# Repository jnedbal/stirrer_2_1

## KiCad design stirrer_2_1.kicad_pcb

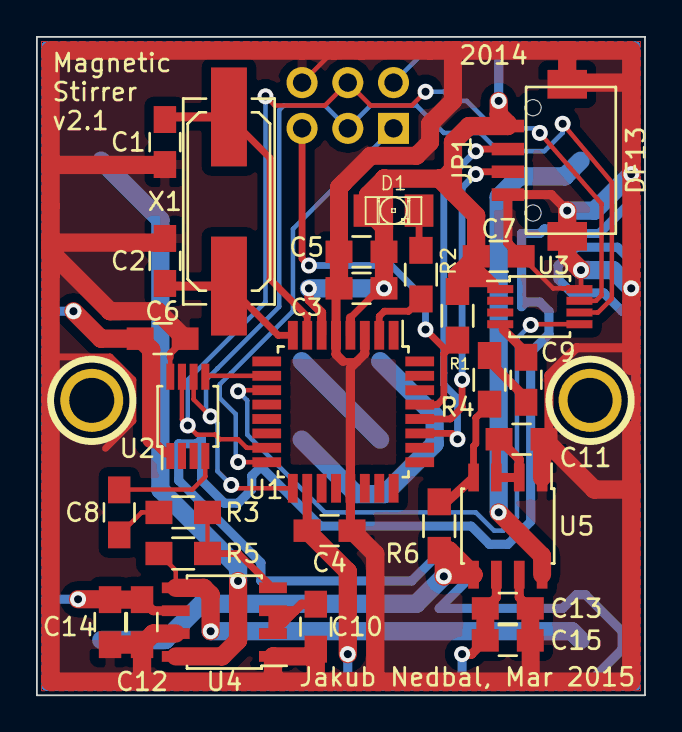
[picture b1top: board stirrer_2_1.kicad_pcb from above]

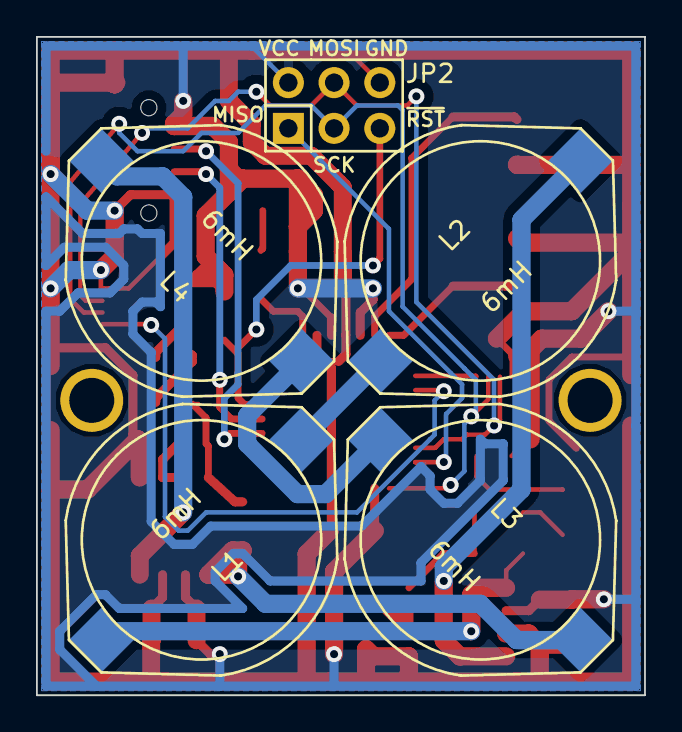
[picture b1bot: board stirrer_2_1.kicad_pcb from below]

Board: 2 copper layers, 33.8 x 36.6 mm, 36 parts (5 on the bottom side), 28 nets.

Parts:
C1, C2: 18p; C_0805_HandSoldering
C3, C4, C6, C7, C12, C13: 100n; C_0805_HandSoldering
C5, C8, C9, C14, C15: 10u; C_0805_HandSoldering
C10, C11: 470n; C_0805_HandSoldering
D1: LED 1206 yel; LED-1206
JP1: DF13; DF13-4P-1.25H
JP2: CONN_3X2; Pin_Header_Straight_2x03
L1, L2, L3, L4: 6mH; 6mH_coil
P1, P2: CONN_1; 1pin
R1: 10k; R_0805_HandSoldering
R2: 470R; R_0805_HandSoldering
R3, R4: 33k; R_0805_HandSoldering
R5, R6: 22k; R_0805_HandSoldering
U1: ATMEGA328P; TQFP-32_7x7mm_Pitch0.8mm
U2, U3: DAC101S101; MSOP-8_3x3mm_Pitch0.65mm
U4, U5: TPA301; SOIC-8_3.9x4.9mm_Pitch1.27mm
X1: 8.000MHz; Q_49U3HMS

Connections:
/MISO: JP2.1, U1.16
/RESET: JP2.5, R1.2, U1.29
/powerModule_2_1/AIN1: C8.2, R3.1
/powerModule_2_1/AIN2: C9.2, R4.1
/powerModule_2_1/DACOUT1: C8.1, U2.4
/powerModule_2_1/DACOUT2: C9.1, U3.4
/powerModule_2_1/IN1+: C10.1, U4.2, U4.3
/powerModule_2_1/IN1-: R3.2, R5.1, U4.4
/powerModule_2_1/IN2+: C11.1, U5.2, U5.3
/powerModule_2_1/IN2-: R4.2, R6.1, U5.4
/powerModule_2_1/L12_VO+: L1.1, R5.2, U4.5
/powerModule_2_1/L12_VO-: L2.1, U4.8
/powerModule_2_1/L34_VO+: L3.1, R6.2, U5.5
/powerModule_2_1/L34_VO-: L4.1, U5.8
/powerModule_2_1/MOSI: JP2.4, U1.15, U2.7, U3.7
/powerModule_2_1/SCK: JP2.3, U1.17, U2.6, U3.6
/powerModule_2_1/~CS_DAC1: U1.10, U2.5
/powerModule_2_1/~CS_DAC2: U1.11, U3.5
GND: C1.2, C2.2, C3.2, C4.2, C5.2, C6.2, C7.2, C10.2, C11.2, C12.2, C13.2, C14.2, C15.2, JP1.4, JP1.5, JP1.6, JP2.6, U1.3, U1.5, U1.21, U2.8, U3.8, U4.1, U4.7, U5.1, U5.7
unnamed: C1.1, U1.7, X1.1
unnamed: C2.1, U1.8, X1.2
unnamed: D1.2, R2.1
unnamed: JP1.2, U1.27
unnamed: JP1.3, U1.28
unnamed: L1.2, L2.2
unnamed: L3.2, L4.2
unnamed: R2.2, U1.2
VCC: C3.1, C4.1, C5.1, C6.1, C7.1, C12.1, C13.1, C14.1, C15.1, D1.1, JP1.1, JP2.2, R1.1, U1.4, U1.6, U1.18, U2.1, U3.1, U4.6, U5.6

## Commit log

2015-03-08 Initial commit. Turned arou inductors, made 2.5mm mounting holes.
2015-03-08 Fixed fron renders.
2017-05-31 Added .gitignore
2017-05-31 updated .gitignore
2017-05-31 Added license
